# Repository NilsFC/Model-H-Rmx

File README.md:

# **Model H Remix 2.0**

## Replacement Model M controller board

Project wiki: https://github.com/NilsFC/Model-H-Rmx/wiki

## **What's new in 2.0?**

-The "Notch": increased compatibility with all Model M cases;<br>
-The "Experimental Area": on-board support to Solenoid;<br>
-The "Testpoints": all testpoint grouped together with Solenoid and one extra I/O available to users;<br>

## **Description**

This board is a direct replacement controller for the classic IBM Model M keyboards.<br>
Old mechanical keyboards are making a comeback among enthusiasts and programmers and gaining value.<br>
Unfortunately, modern computers no longer have DIN or PS2 ports, so there’s no simple way to connect a 40-year-old hardware to a brand-new laptop.<br>
By replacing the legacy electronics inside the keyboard, it’s possible to revive a “piece of history” and even add modern functions like USB connectivity and remappable characters. The original PCB can be preserved to revert the keyboard to its original state.<br>

The "Model H Remix" is designed to fit and work with standard 101/102/85/86 keys keyboards.<br>

## **Credits**

This version is just a rework of the original design from **John Hawthorn**. <br>
Check out the fantastic work of this guy to whom I am very grateful. Thanks to his Open Source project I really learned a lot. [Model H Project](https://modelh.club/)
<br>

Gratitude goes also to **Jerome Berclaz** for his update work on the Model H software in QMK and QMK-Vial firmware. https://github.com/jberclaz/modelh

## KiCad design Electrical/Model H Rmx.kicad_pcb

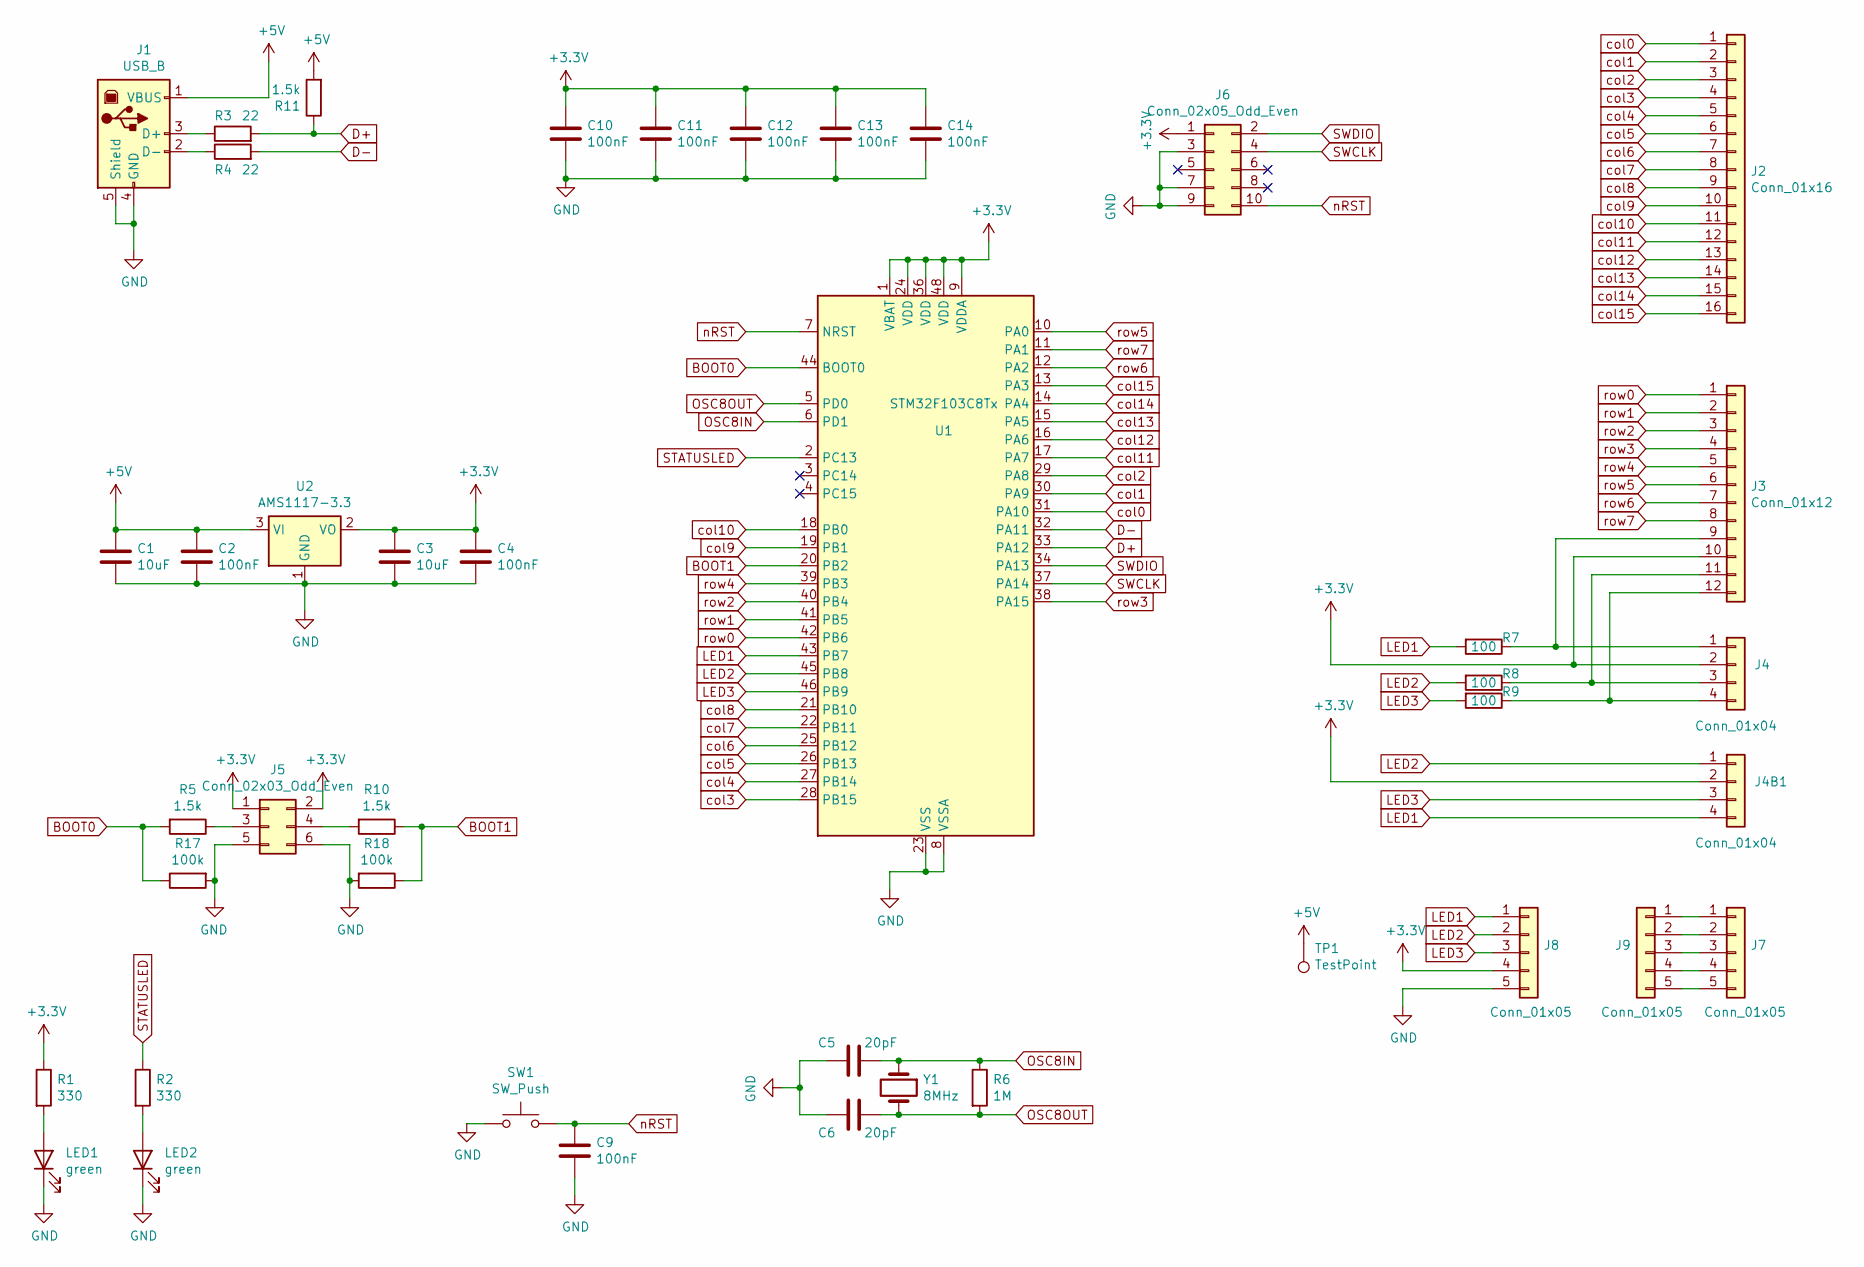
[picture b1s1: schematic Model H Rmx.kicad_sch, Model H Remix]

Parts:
C1, C3: 10uF; C_0603_1608Metric; LCSC C19702
C2, C4, C9, C10, C11, C12, C13, C14: 100nF; C_0603_1608Metric; LCSC C1525
C5, C6: 20pF; C_0603_1608Metric; LCSC C1653
J1: USB_B; USB_B_OST_USB-B1HSxx_Horizontal
J2: Conn_01x16; Model1-triomate-cols16
J3: Conn_01x12; Model1-triomate-rows12
J4: Conn_01x04; Model1-triomate-leds4
J4B1: Conn_01x04; JST_EH_S4B-EH_1x04_P2.50mm_Horizontal
J5: Conn_02x03_Odd_Even; PinHeader_2x03_P2.54mm_Vertical
J6: Conn_02x05_Odd_Even; IDC-Header_2x05_P2.54mm_Vertical
J7, J8, J9: Conn_01x05; PinSocket_1x05_P2.54mm_Vertical
LED1, LED2: green; LED_0805_2012Metric; LCSC C2297
R1, R2: 330; R_0603_1608Metric; LCSC C23138
R3, R4: 22; R_0603_1608Metric; LCSC C23345
R5, R10, R11: 1.5k; R_0603_1608Metric; LCSC C22843
R6: 1M; R_0603_1608Metric; LCSC C22935
R7, R8, R9: 100; R_0805_2012Metric; LCSC C17408
R17, R18: 100k; R_0603_1608Metric; LCSC C25803
SW1: SW_Push; SW_SPST_EVPBF; LCSC C318888
TP1: TestPoint; TestPoint_THTPad_D1.5mm_Drill0.7mm
U1: STM32F103C8Tx; LQFP-48_7x7mm_P0.5mm; LCSC C8734
U2: AMS1117-3.3; SOT-223-3_TabPin2; LCSC C6186
Y1: 8MHz; Crystal_SMD_5032-2Pin_5.0x3.2mm; LCSC C115962

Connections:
+3.3V: C3.1, C4.1, C10.1, C11.1, C12.1, C13.1, C14.1, J3.10, J4.2, J4B1.2, J5.1, J5.2, J6.1, J8.4, R1.1, U1.1 (VBAT), U1.9 (VDDA), U1.24 (VDD), U1.36 (VDD), U1.48 (VDD), U2.2 (VO)
+5V: C1.1, C2.1, J1.1 (VBUS), R11.2, TP1.1, U2.3 (VI)
BOOT0: R5.2, R17.1, U1.44 (BOOT0)
BOOT1: R10.1, R18.1, U1.20 (PB2)
D+: R3.2, R11.1, U1.33 (PA12)
D-: R4.2, U1.32 (PA11)
GND: C1.2, C2.2, C3.2, C4.2, C5.2, C6.2, C9.2, C10.2, C11.2, C12.2, C13.2, C14.2, J1.4 (GND), J1.5 (Shield), J5.5, J5.6, J6.3, J6.7, J6.9, J8.5, LED1.1 (K), LED2.1 (K), R17.2, R18.2, SW1.1, U1.8 (VSSA), U1.23 (VSS), U1.35 (VSS), U1.47 (VSS), U2.1 (GND)
LED1: J4B1.4, J8.1, R7.2, U1.43 (PB7)
LED2: J4B1.1, J8.2, R8.2, U1.45 (PB8)
LED3: J4B1.3, J8.3, R9.2, U1.46 (PB9)
unnamed: J1.3 (D+), R3.1
unnamed: J1.2 (D-), R4.1
unnamed: J3.9, J4.1, R7.1
unnamed: J3.11, J4.3, R8.1
unnamed: J3.12, J4.4, R9.1
unnamed: J5.3, R5.1
unnamed: J5.4, R10.2
unnamed: J7.1, J9.1
unnamed: J7.2, J9.2
unnamed: J7.3, J9.3
unnamed: J7.4, J9.4
unnamed: J7.5, J9.5
unnamed: LED1.2 (A), R1.2
unnamed: LED2.2 (A), R2.2
OSC8IN: C5.1, R6.1, U1.6 (PD1), Y1.1
OSC8OUT: C6.1, R6.2, U1.5 (PD0), Y1.2
STATUSLED: R2.1, U1.2 (PC13)
SWCLK: J6.4, U1.37 (PA14)
SWDIO: J6.2, U1.34 (PA13)
col0: J2.1, U1.31 (PA10)
col1: J2.2, U1.30 (PA9)
col2: J2.3, U1.29 (PA8)
col3: J2.4, U1.28 (PB15)
col4: J2.5, U1.27 (PB14)
col5: J2.6, U1.26 (PB13)
col6: J2.7, U1.25 (PB12)
col7: J2.8, U1.22 (PB11)
col8: J2.9, U1.21 (PB10)
col9: J2.10, U1.19 (PB1)
col10: J2.11, U1.18 (PB0)
col11: J2.12, U1.17 (PA7)
col12: J2.13, U1.16 (PA6)
col13: J2.14, U1.15 (PA5)
col14: J2.15, U1.14 (PA4)
col15: J2.16, U1.13 (PA3)
nRST: C9.1, J6.10, SW1.2, U1.7 (NRST)
row0: J3.1, U1.42 (PB6)
row1: J3.2, U1.41 (PB5)
row2: J3.3, U1.40 (PB4)
row3: J3.4, U1.38 (PA15)
row4: J3.5, U1.39 (PB3)
row5: J3.6, U1.10 (PA0)
row6: J3.7, U1.12 (PA2)
row7: J3.8, U1.11 (PA1)

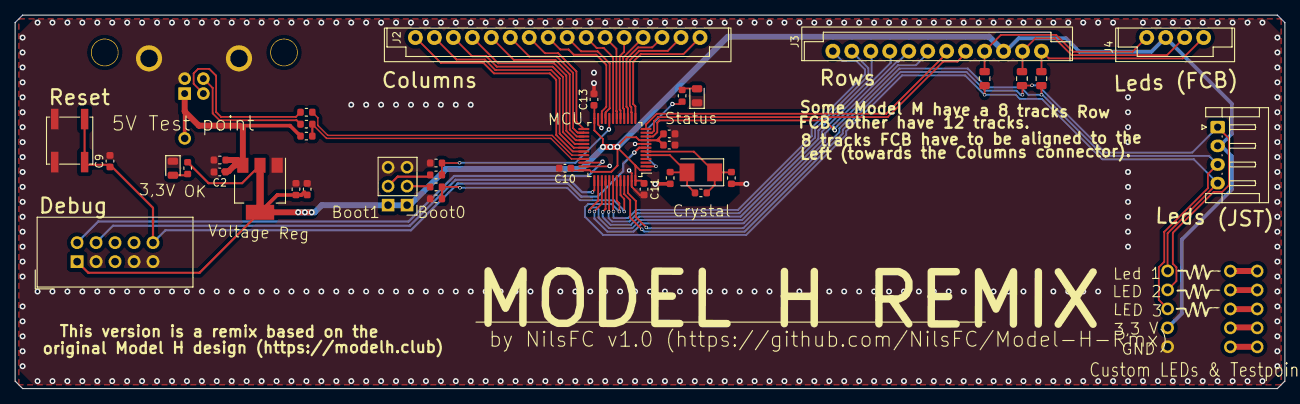
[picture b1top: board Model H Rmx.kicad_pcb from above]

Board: 2 copper layers, 170.0 x 50.0 mm, 42 parts (0 on the bottom side), 54 nets.

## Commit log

2025-02-20 Initial changes to this fork description.
2025-03-01 Sync test
2025-03-01 Started documenting
2025-03-01 Updated image
2025-03-02 PCB Files, Software, Schematics
2025-03-02 File upload
2025-03-05 Software Update
2025-03-06 Credits update
2025-03-06 Credits
2025-03-31 Pics
2025-05-22 Updated Firmware zip file content
2025-09-01 v2.0
